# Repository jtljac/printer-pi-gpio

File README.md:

A simple break-out board for a Raspberry Pi that makes accessing some GPIO interfaces easier for [klipper](https://www.klipper3d.org/).

## Features
5V Power in via screw terminal for powering Pi.

UART Bus for connecting klipper directly to a control board via serial.  
The UART bus also has 2 pins for 5V, which depending on your control board can power the Pi (In my case, the [SKR-Pico](https://github.com/bigtreetech/SKR-Pico) supports this). This can be enabled using the `UART Power Enable` jumper.

Reverse current protection on both power inputs, also doubling as Power Or-ing, allowing both power inputs to be powered simultaniously safely.

LED indicators on each power input to indicate when each one is powered.

SPI bus split into 2 connectors with different CS pins (`spi0: GPIO8`, `spi1: GPIO7`), for screens and ADXLs.

I2C bus for miscellaneous purposes.

A header for connecting to a Relay Module to toggle power to the actual printer, uses `GPIO17`.  
Also features an LED to indicate when the relay is toggled.

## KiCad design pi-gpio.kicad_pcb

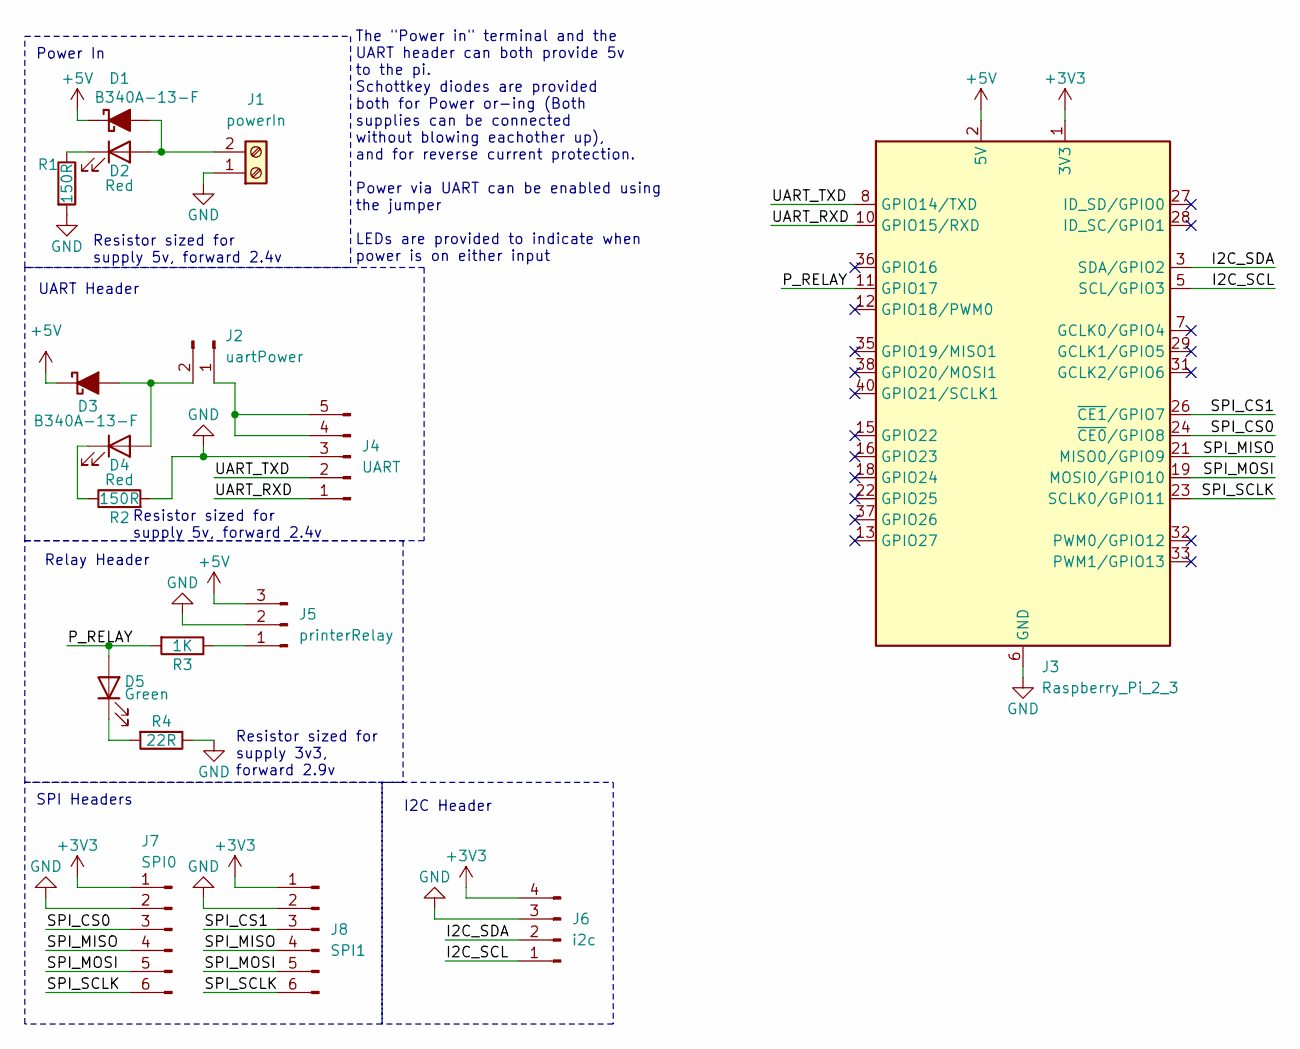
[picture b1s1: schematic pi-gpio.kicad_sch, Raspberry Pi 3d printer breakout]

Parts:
D1, D3: B340A-13-F; D_SMA_Handsoldering
D2, D4: Red; LED_0805_2012Metric
D5: Green; LED_0805_2012Metric
J1: powerIn; TerminalBlock_MAX_MX127-5.0-02P_1x02_P5.00mm
J2: uartPower; PinHeader_1x02_P2.54mm_Vertical
J3: Raspberry_Pi_2_3; RaspberryPi_Zero_BoardLayout
J4: UART; JST_XH_B5B-XH-A_1x05_P2.50mm_Vertical
J5: printerRelay; JST_XH_B3B-XH-A_1x03_P2.50mm_Vertical
J6: i2c; JST_XH_B4B-XH-A_1x04_P2.50mm_Vertical
J7: SPI0; JST_PH_B6B-PH-K_1x06_P2.00mm_Vertical
J8: SPI1; JST_PH_B6B-PH-K_1x06_P2.00mm_Vertical
R1, R2: 150R; R_0805_2012Metric_Pad1.20x1.40mm_HandSolder
R3: 1K; R_0805_2012Metric_Pad1.20x1.40mm_HandSolder
R4: 22R; R_0805_2012Metric_Pad1.20x1.40mm_HandSolder

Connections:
+3V3: J3.1 (3V3), J3.17 (3V3), J6.4, J7.1, J8.1
+5V: D1.1 (K), D3.1 (K), J3.2 (5V), J3.4 (5V), J5.3
/I2C_SCL: J3.5 (SCL/GPIO3), J6.1
/I2C_SDA: J3.3 (SDA/GPIO2), J6.2
/P_RELAY: D5.2 (A), J3.11 (GPIO17), R3.2
/SPI_CS0: J3.24 (~CE0/GPIO8), J7.3
/SPI_CS1: J3.26 (~CE1/GPIO7), J8.3
/SPI_MISO: J3.21 (MISO0/GPIO9), J7.4, J8.4
/SPI_MOSI: J3.19 (MOSI0/GPIO10), J7.5, J8.5
/SPI_SCLK: J3.23 (SCLK0/GPIO11), J7.6, J8.6
/UART_RXD: J3.10 (GPIO15/RXD), J4.1
/UART_TXD: J3.8 (GPIO14/TXD), J4.2
GND: J1.1, J3.6 (GND), J3.9 (GND), J3.14 (GND), J3.20 (GND), J3.25 (GND), J3.30 (GND), J3.34 (GND), J3.39 (GND), J4.3, J5.2, J6.3, J7.2, J8.2, R1.2, R2.2, R4.1
unnamed: D1.2 (A), D2.2 (A), J1.2
unnamed: D2.1 (K), R1.1
unnamed: D3.2 (A), D4.2 (A), J2.2
unnamed: D4.1 (K), R2.1
unnamed: D5.1 (K), R4.2
unnamed: J2.1, J4.4, J4.5
unnamed: J5.1, R3.1

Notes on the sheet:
Resistor sized for supply 5v, forward 2.4v
Relay Header
Power In
Resistor sized for supply 3v3, forward 2.9v
The "Power in" terminal and the UART header can both provide 5v to the pi. Schottkey diodes are provided both for Power or-ing (Both supplies can be connected without blowing eachother up), and for reverse current protection. Power via UART can be enabled using the jumper LEDs are provided to indic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
I2C Header
UART Header
SPI Headers

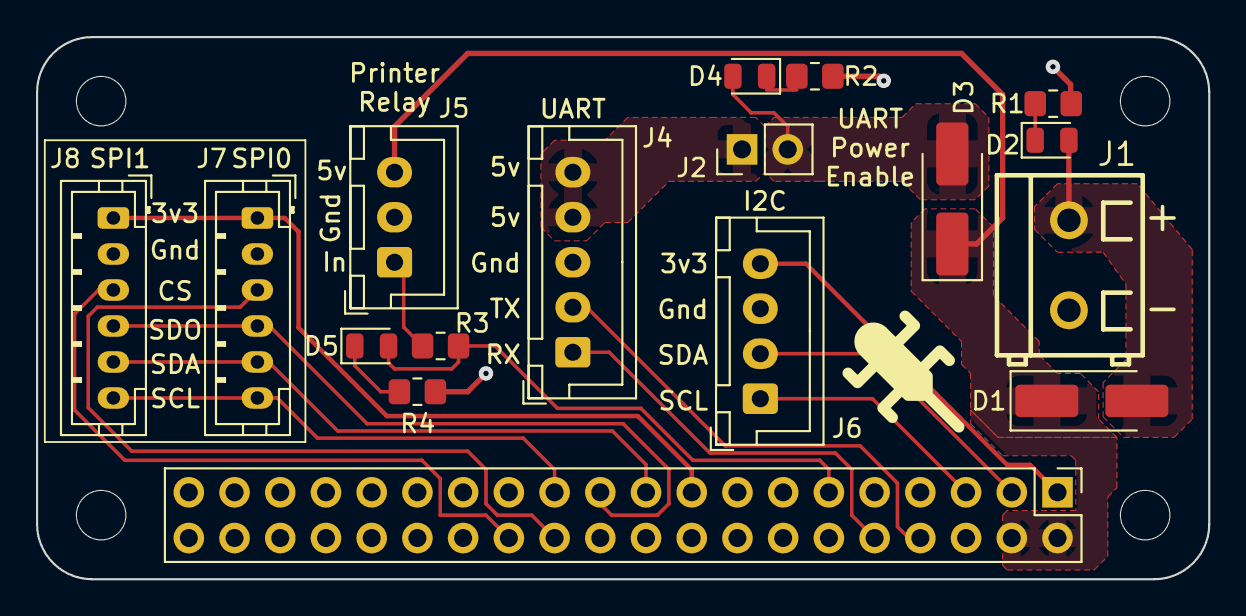
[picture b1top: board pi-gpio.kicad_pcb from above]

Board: 2 copper layers, 65.1 x 30.1 mm, 17 parts (1 on the bottom side), 20 nets.

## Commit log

2025-08-17 Doubled SPI headers, added I2C
2025-08-17 Added readme
2025-08-17 reworded readme
